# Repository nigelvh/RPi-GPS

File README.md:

# GPS Board for Standard Form-Factor RPi Boards
This is a small custom board for use with standard form-factor RPi single board computers.

This is not a wholly unique device, there are other devices that perform similar functions or some subset thereof. It is certainly not the only way to accomplish the task.

This device uses a good quality GPS receiver with precise Pulse Per Second (PPS) output, and exposes both the NMEA data on the RPi's serial port, as well as the PPS signal on GPIO 4.

The schematic and board files have been created in Eagle, though I cannot guarantee how they will load without all the the associated libraries. There are additionally exported images of the schematic and board designs available for reference without using the Eagle software package.

A parts text file has been included which contains DigiKey links for each part. These are certainly not the only parts that would work, or the links over time may end up referencing parts that are out of stock. Any adjustments are left as an exercise to the reader.

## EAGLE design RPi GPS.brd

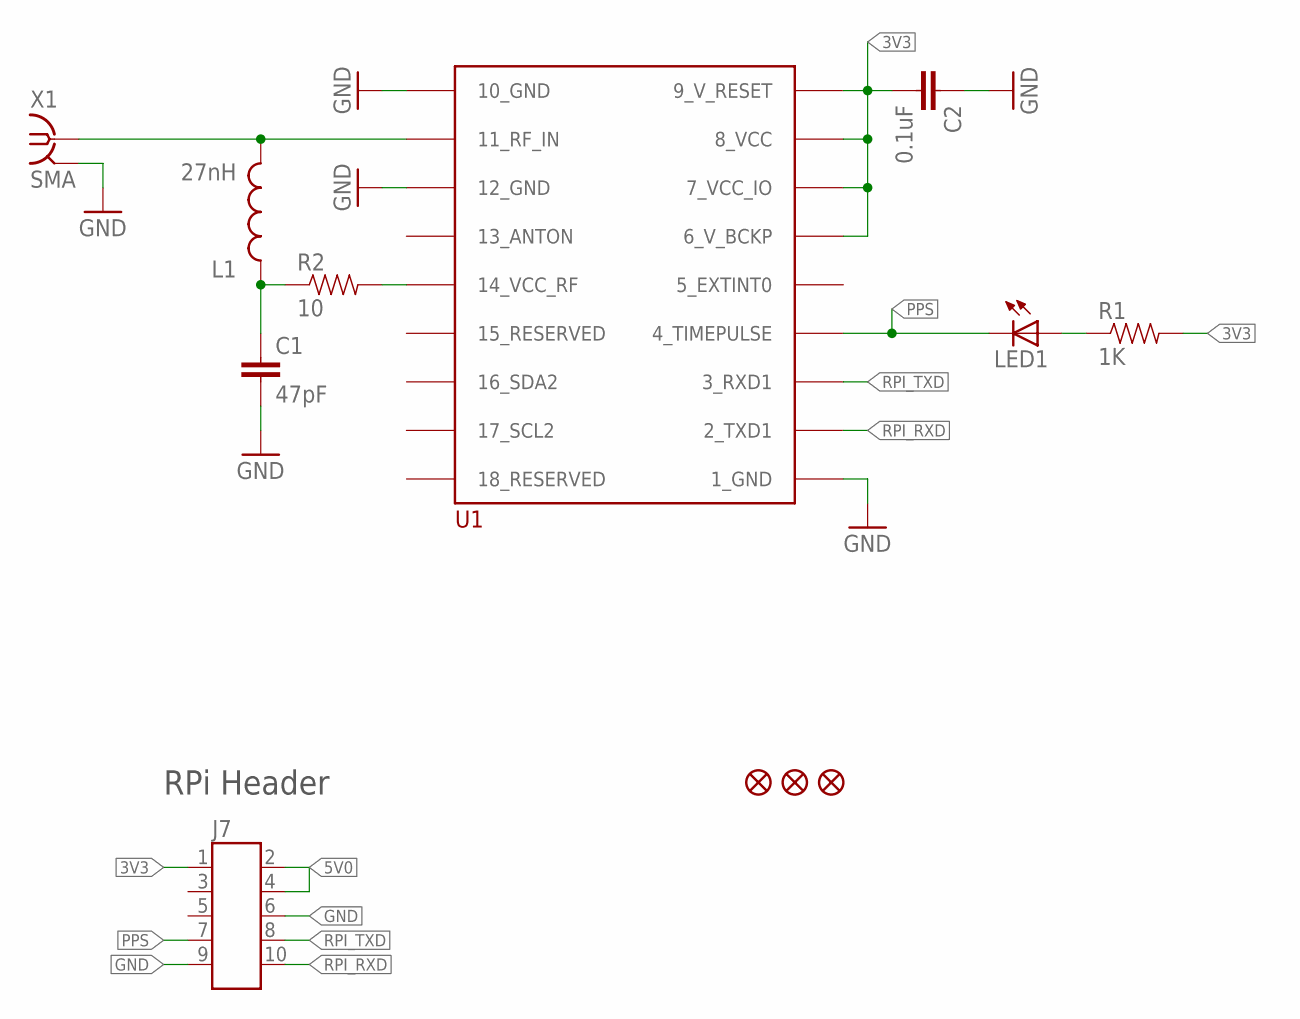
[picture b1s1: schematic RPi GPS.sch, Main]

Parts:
C1: 47pF; 0603-CAP
C2: 0.1uF; 0603-CAP
FID2, FID3, FID4: FIDUCIAL
J7: HEADER-2X5-0.1; HEADER-2X5
L1: 27nH; 0603
LED1: LED0603; LED-0603
R1: 1K; 0603-RES
R2: 10; 0603-RES
U1: UBLOX_MAX
X1: SMA; SMA_EDGE

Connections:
3V3: C2.2, J7.1, R1.2, U1.6_V_BCKP, U1.7_VCC_IO, U1.8_VCC, U1.9_V_RESET
5V0: J7.2, J7.4
GND: C1.2, C2.1, J7.6, J7.9, U1.1_GND, U1.10_GND, U1.12_GND, X1.GND@1 (2), X1.GND@2 (2), X1.GND@3 (2), X1.GND@4 (2)
unnamed: L1.2, U1.11_RF_IN, X1.SIG (1)
unnamed: LED1.A, R1.1
unnamed: R2.2, U1.14_VCC_RF
unnamed: C1.1, L1.1, R2.1
PPS: J7.7, LED1.C, U1.4_TIMEPULSE
RPI_RXD: J7.10, U1.2_TXD1
RPI_TXD: J7.8, U1.3_RXD1

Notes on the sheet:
RPi Header

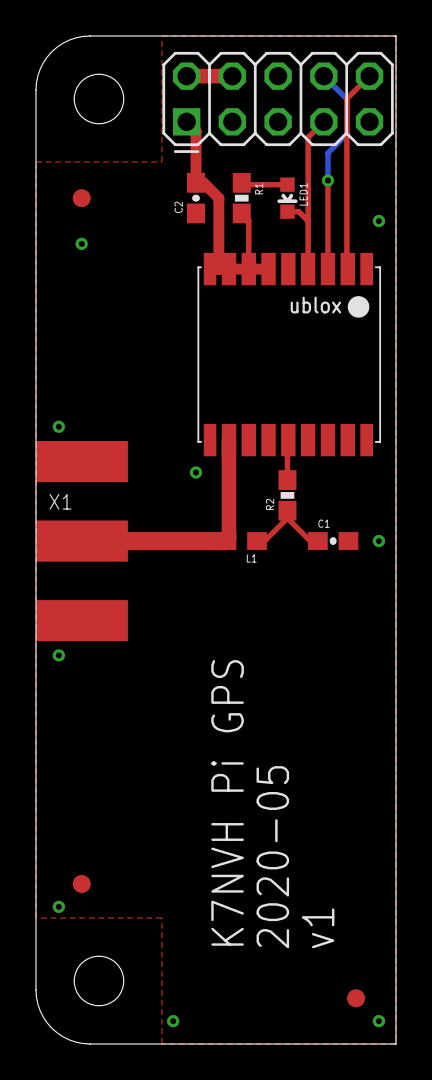
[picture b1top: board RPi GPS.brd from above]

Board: 2 copper layers, 20.0 x 56.0 mm, 12 parts (0 on the bottom side), 10 nets.

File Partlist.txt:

Part     Value          Device           Package    	Digikey Link
C1       47pF           CAP0603-CAP      0603-CAP   	https://www.digikey.com/en/products/detail/yageo/CC0603JRNPO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
C2       0.1uF          CAP0603-CAP      0603-CAP   	https://www.digikey.com/en/products/detail/samsung-electro-m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

J7       HEADER-2X5-0.1 HEADER-2X5-0.1   HEADER-2X5 	https://www.digikey.com/en/products/detail/sullins-connector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

L1       27nH           INDUCTOR0603     0603       	https://www.digikey.com/en/products/detail/murata-electronic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

LED1                    LED0603          LED-0603   	https://www.digikey.com/en/products/detail/w%C3%BCrth-elektr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

R1       1K             RESISTOR0603-RES 0603-RES   	https://www.digikey.com/en/products/detail/stackpole-electro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
R2       10             RESISTOR0603-RES 0603-RES   	https://www.digikey.com/en/products/detail/stackpole-electro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

U1       UBLOX_MAX      UBLOX_MAX        UBLOX_MAX  	https://www.digikey.com/en/products/detail/u-blox/MAX-M8C-0/6150635

X1       SMA            SMA              SMA_EDGE   	https://www.digikey.com/en/products/detail/cinch-connectivit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

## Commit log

2023-04-04 Add all the project files.
2023-04-04 Rotate and crop board images.
2023-04-04 Replacing old board images.

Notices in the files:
parts and their libraries:
SparkFun: Licensing: CC v3.0 Share-Alike You are welcome to use this library for commercial purposes.
